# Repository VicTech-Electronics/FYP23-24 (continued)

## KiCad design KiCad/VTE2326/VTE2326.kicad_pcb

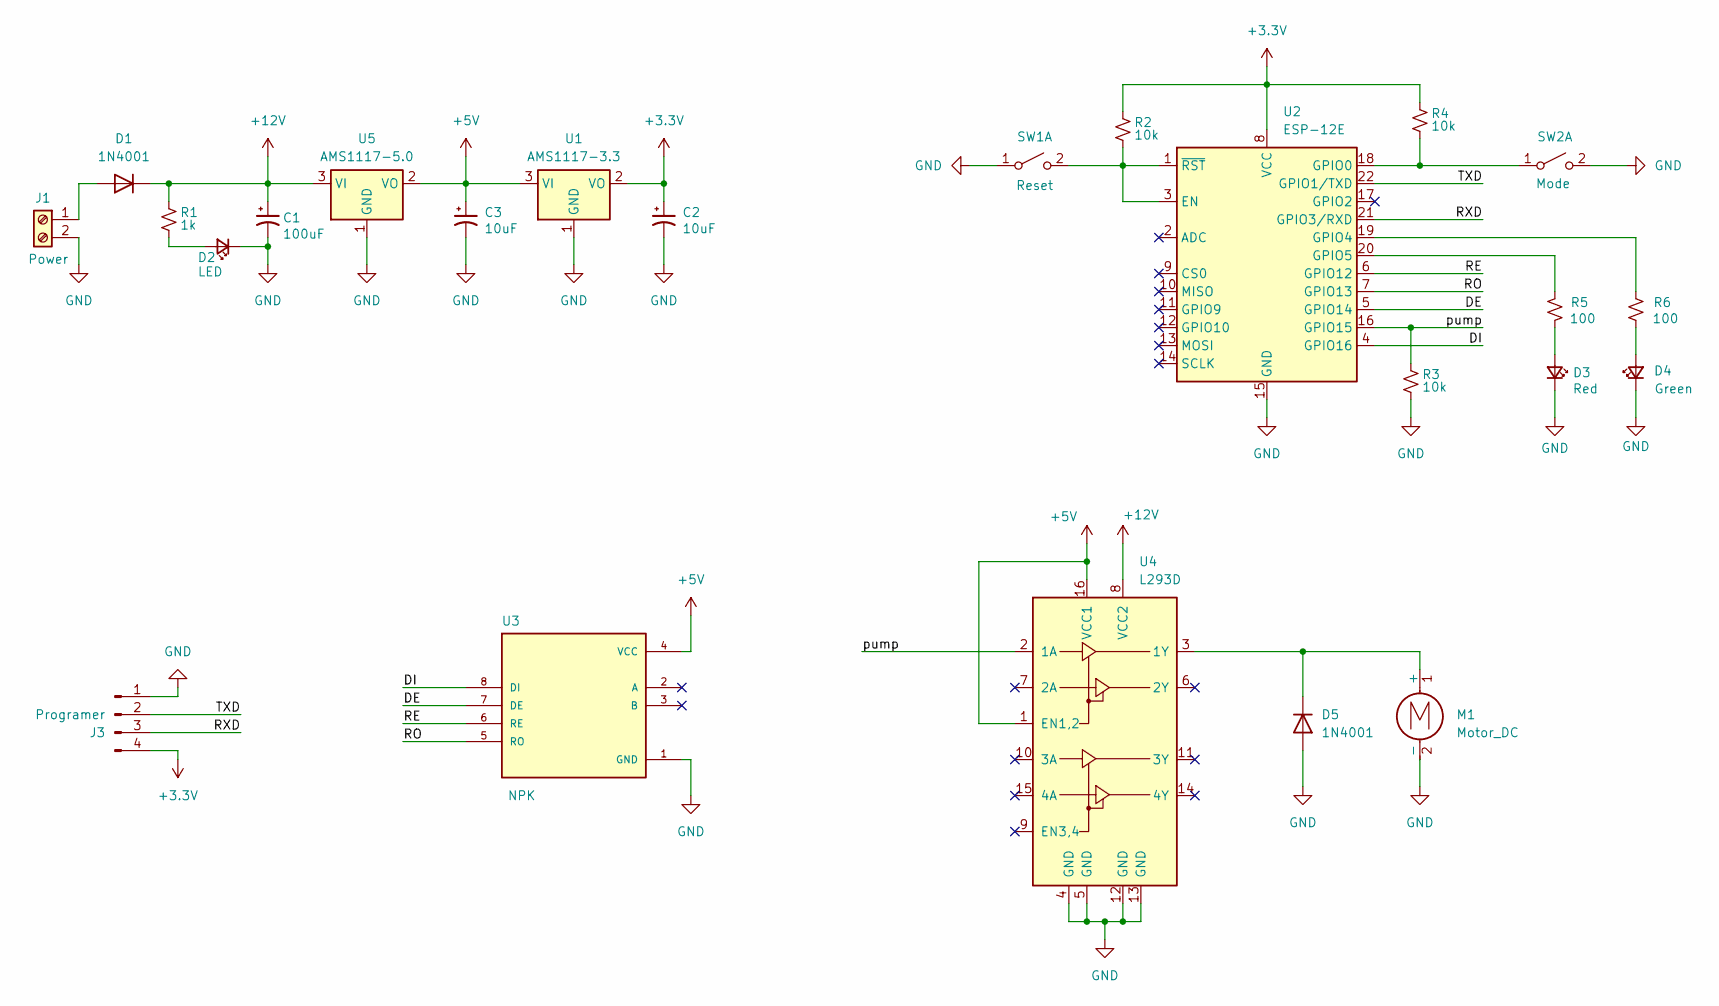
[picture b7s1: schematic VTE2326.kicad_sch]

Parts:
C1: 100uF; CP_Radial_D4.0mm_P2.00mm
C2, C3: 10uF; CP_Radial_D4.0mm_P2.00mm
D1, D5: 1N4001; D_DO-41_SOD81_P10.16mm_Horizontal
D2: LED; LED_D3.0mm_Clear
D3: Red; LED_D3.0mm_Clear
D4: Green; LED_D3.0mm_Clear
J1: Power; TerminalBlock_bornier-2_P5.08mm
J3: Programer; PinHeader_1x04_P2.54mm_Vertical
M1: Motor_DC; TerminalBlock_bornier-2_P5.08mm
R1: 1k; R_Axial_DIN0207_L6.3mm_D2.5mm_P10.16mm_Horizontal
R2, R3, R4: 10k; R_Axial_DIN0207_L6.3mm_D2.5mm_P10.16mm_Horizontal
R5, R6: 100; R_Axial_DIN0207_L6.3mm_D2.5mm_P10.16mm_Horizontal
SW1: Reset; SW_PUSH_6mm
SW2: Mode; SW_PUSH_6mm
U1: AMS1117-3.3; SOT-223-3_TabPin2
U2: ESP-12E
U3: NPK; MODULE_MAX485_MODULE_5V_LOGIC_TLL_TO_RS-485_CONVERTER; PARTREV 1r0
U4: L293D; DIP-16_W7.62mm
U5: AMS1117-5.0; SOT-223-3_TabPin2

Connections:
+3.3V: C2.1, J3.4, R2.1, R4.1, U1.2 (VO), U2.8 (VCC)
+5V: C3.1, U1.3 (VI), U3.4 (VCC), U4.1 (EN1,2), U4.16 (VCC1), U5.2 (VO)
+12V: C1.1, D1.1 (K), R1.1, U4.8 (VCC2), U5.3 (VI)
/DE: U2.5 (GPIO14), U3.7 (DE)
/DI: U2.4 (GPIO16), U3.8 (DI)
/RE: U2.6 (GPIO12), U3.6 (RE)
/RO: U2.7 (GPIO13), U3.5 (RO)
/RXD: J3.3, U2.21 (GPIO3/RXD)
/TXD: J3.2, U2.22 (GPIO1/TXD)
/pump: R3.1, U2.16 (GPIO15), U4.2 (1A)
GND: C1.2, C2.2, C3.2, D2.1 (K), D3.1 (K), D4.1 (K), D5.2 (A), J1.2, J3.1, M1.2 (-), R3.2, SW1.1 (A), SW2.2 (B), U1.1 (GND), U2.15 (GND), U3.1 (GND), U4.4 (GND), U4.5 (GND), U4.12 (GND), U4.13 (GND), U5.1 (GND)
unnamed: D1.2 (A), J1.1
unnamed: D2.2 (A), R1.2
unnamed: D3.2 (A), R5.2
unnamed: D4.2 (A), R6.1
unnamed: D5.1 (K), M1.1 (+), U4.3 (1Y)
unnamed: R2.2, SW1.2 (B), U2.1 (~RST), U2.3 (EN)
unnamed: R4.2, SW2.1 (A), U2.18 (GPIO0)
unnamed: R6.2, U2.19 (GPIO4)
unnamed: R5.1, U2.20 (GPIO5)

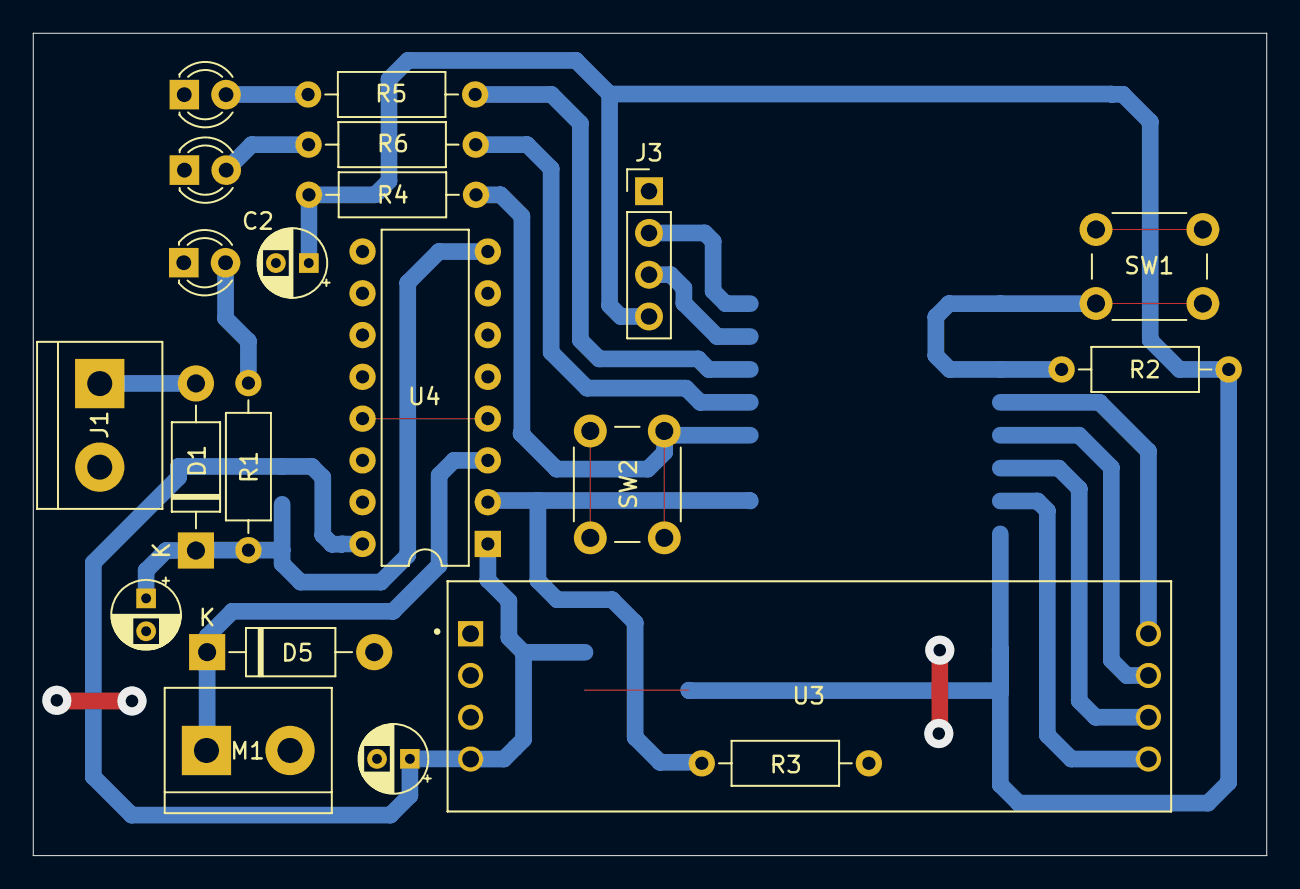
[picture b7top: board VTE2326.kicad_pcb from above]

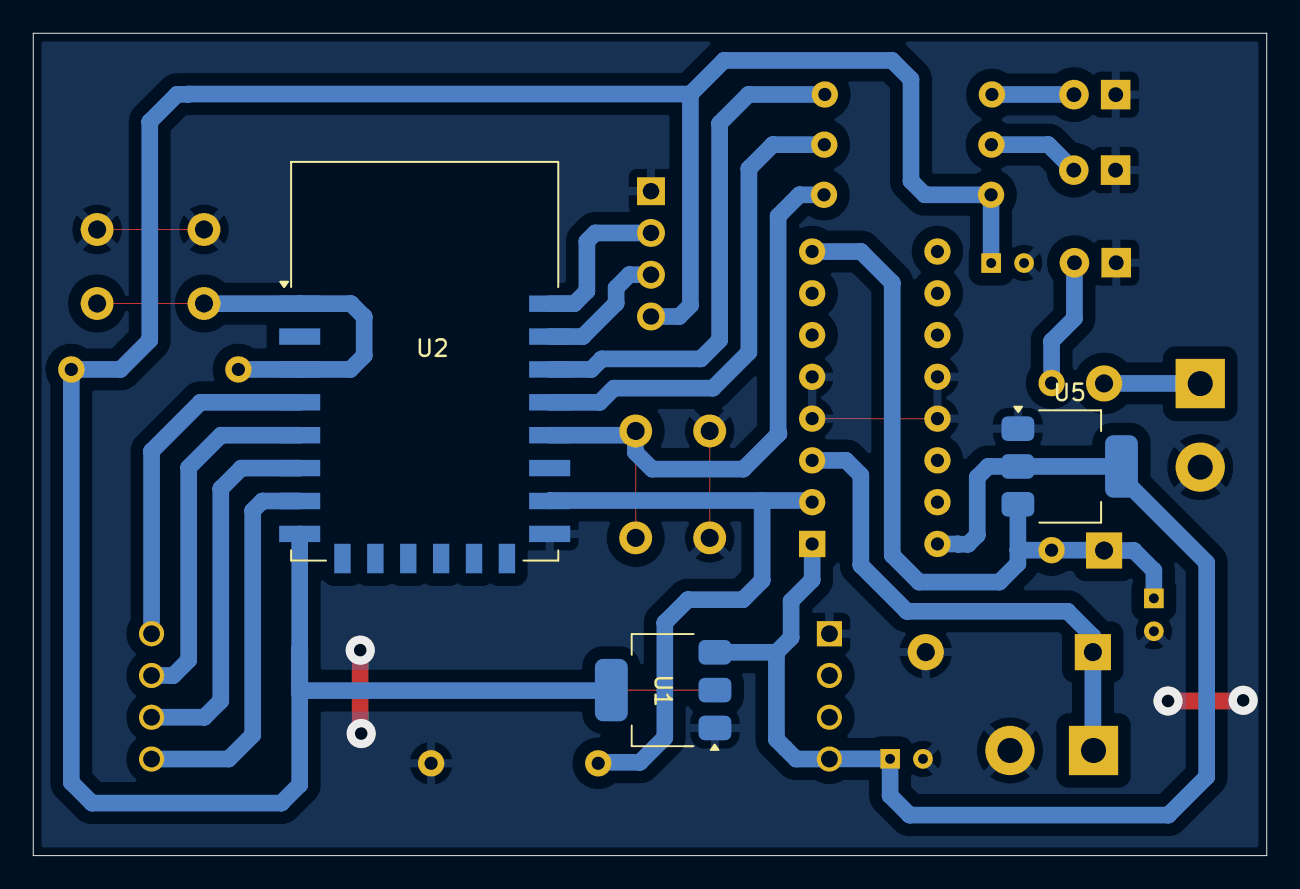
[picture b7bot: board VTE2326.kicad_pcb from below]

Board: 2 copper layers, 75.0 x 50.0 mm, 24 parts (3 on the bottom side), 20 nets.

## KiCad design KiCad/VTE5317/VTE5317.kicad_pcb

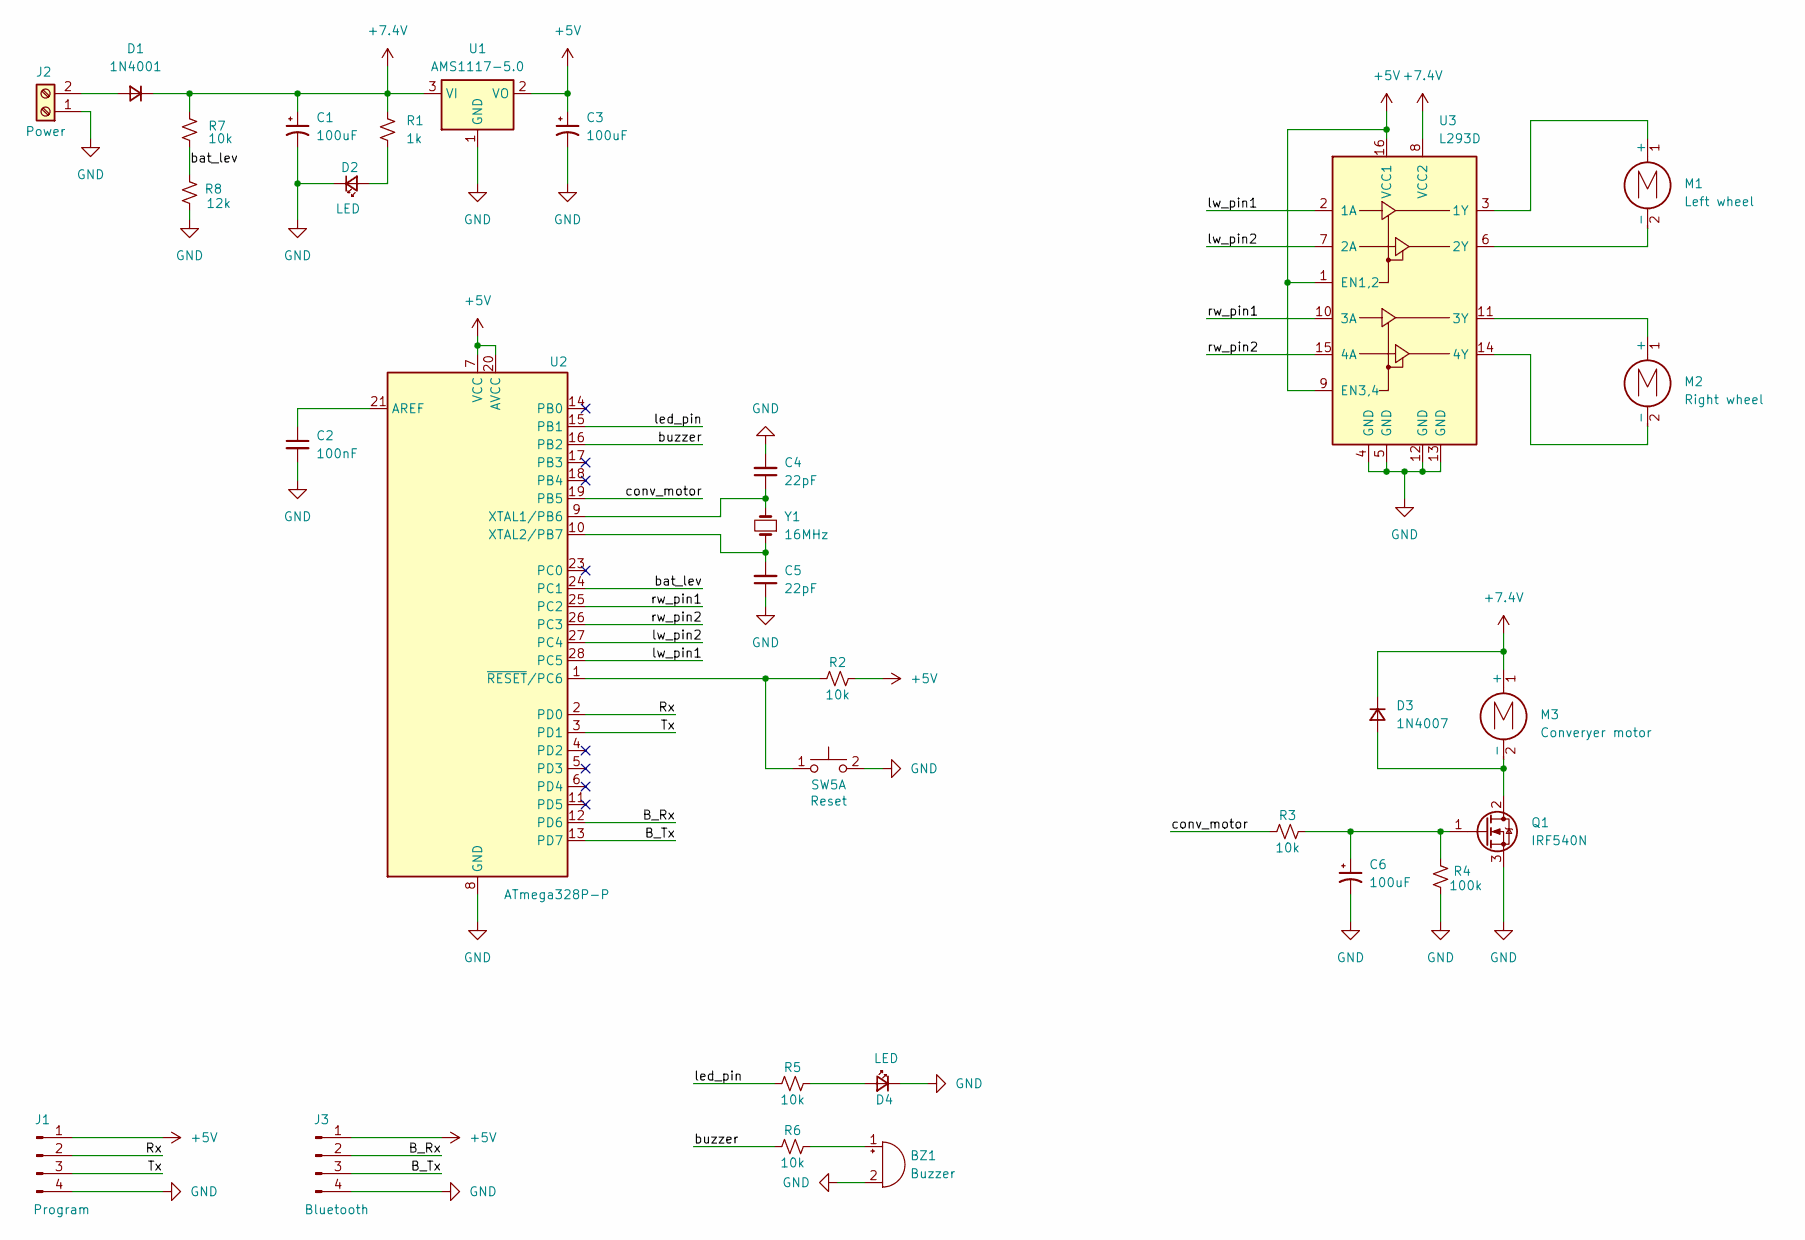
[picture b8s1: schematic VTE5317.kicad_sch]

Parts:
BZ1: Buzzer; Buzzer_12x9.5RM7.6
C1, C3, C6: 100uF; CP_Radial_D5.0mm_P2.50mm
C2: 100nF; C_Disc_D3.0mm_W1.6mm_P2.50mm
C4, C5: 22pF; C_Disc_D3.0mm_W1.6mm_P2.50mm
D1: 1N4001; D_A-405_P10.16mm_Horizontal
D2, D4: LED; LED_D3.0mm
D3: 1N4007; D_A-405_P10.16mm_Horizontal
J1: Program; PinHeader_1x04_P2.54mm_Vertical
J2: Power; TerminalBlock_bornier-2_P5.08mm
J3: Bluetooth; PinHeader_1x04_P2.54mm_Vertical
M1: Left wheel; TerminalBlock_bornier-2_P5.08mm
M2: Right wheel; TerminalBlock_bornier-2_P5.08mm
M3: Converyer motor; TerminalBlock_bornier-2_P5.08mm
Q1: IRF540N; TO-220-3_Vertical
R1: 1k; R_Axial_DIN0207_L6.3mm_D2.5mm_P10.16mm_Horizontal
R2, R3, R5, R6, R7: 10k; R_Axial_DIN0207_L6.3mm_D2.5mm_P10.16mm_Horizontal
R4: 100k; R_Axial_DIN0207_L6.3mm_D2.5mm_P10.16mm_Horizontal
R8: 12k; R_Axial_DIN0207_L6.3mm_D2.5mm_P10.16mm_Horizontal
SW5: Reset; SW_PUSH_6mm
U1: AMS1117-5.0; SOT-223-3_TabPin2
U2: ATmega328P-P; DIP-28_W7.62mm_LongPads
U3: L293D; DIP-16_W7.62mm_Socket_LongPads
Y1: 16MHz; Crystal_HC50_Vertical

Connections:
+5V: C3.1, J1.1, J3.1, R2.2, U1.2 (VO), U2.7 (VCC), U2.20 (AVCC), U3.1 (EN1,2), U3.9 (EN3,4), U3.16 (VCC1)
+7.4V: C1.1, D1.1 (K), D3.1 (K), M3.1 (+), R1.1, R7.1, U1.3 (VI), U3.8 (VCC2)
/B_Rx: J3.2, U2.12 (PD6)
/B_Tx: J3.3, U2.13 (PD7)
/Rx: J1.2, U2.2 (PD0)
/Tx: J1.3, U2.3 (PD1)
/bat_lev: R7.2, R8.1, U2.24 (PC1)
/buzzer: R6.1, U2.16 (PB2)
/conv_motor: R3.1, U2.19 (PB5)
/led_pin: R5.1, U2.15 (PB1)
/lw_pin1: U2.28 (PC5), U3.2 (1A)
/lw_pin2: U2.27 (PC4), U3.7 (2A)
/rw_pin1: U2.25 (PC2), U3.10 (3A)
/rw_pin2: U2.26 (PC3), U3.15 (4A)
GND: BZ1.2 (-), C1.2, C2.2, C3.2, C4.2, C5.1, C6.2, D2.1 (K), D4.1 (K), J1.4, J2.1, J3.4, Q1.3 (S), R4.1, R8.2, SW5.2 (D), U1.1 (GND), U2.8 (GND), U2.22 (GND), U3.4 (GND), U3.5 (GND), U3.12 (GND), U3.13 (GND)
unnamed: BZ1.1 (+), R6.2
unnamed: D1.2 (A), J2.2
unnamed: D2.2 (A), R1.2
unnamed: D3.2 (A), M3.2 (-), Q1.2 (D)
unnamed: D4.2 (A), R5.2
unnamed: M1.1 (+), U3.3 (1Y)
unnamed: M1.2 (-), U3.6 (2Y)
unnamed: M2.1 (+), U3.11 (3Y)
unnamed: M2.2 (-), U3.14 (4Y)
unnamed: C6.1, Q1.1 (G), R3.2, R4.2
unnamed: R2.1, SW5.1 (C), U2.1 (~RESET/PC6)
unnamed: C2.1, U2.21 (AREF)
unnamed: C4.1, U2.9 (XTAL1/PB6), Y1.2
unnamed: C5.2, U2.10 (XTAL2/PB7), Y1.1

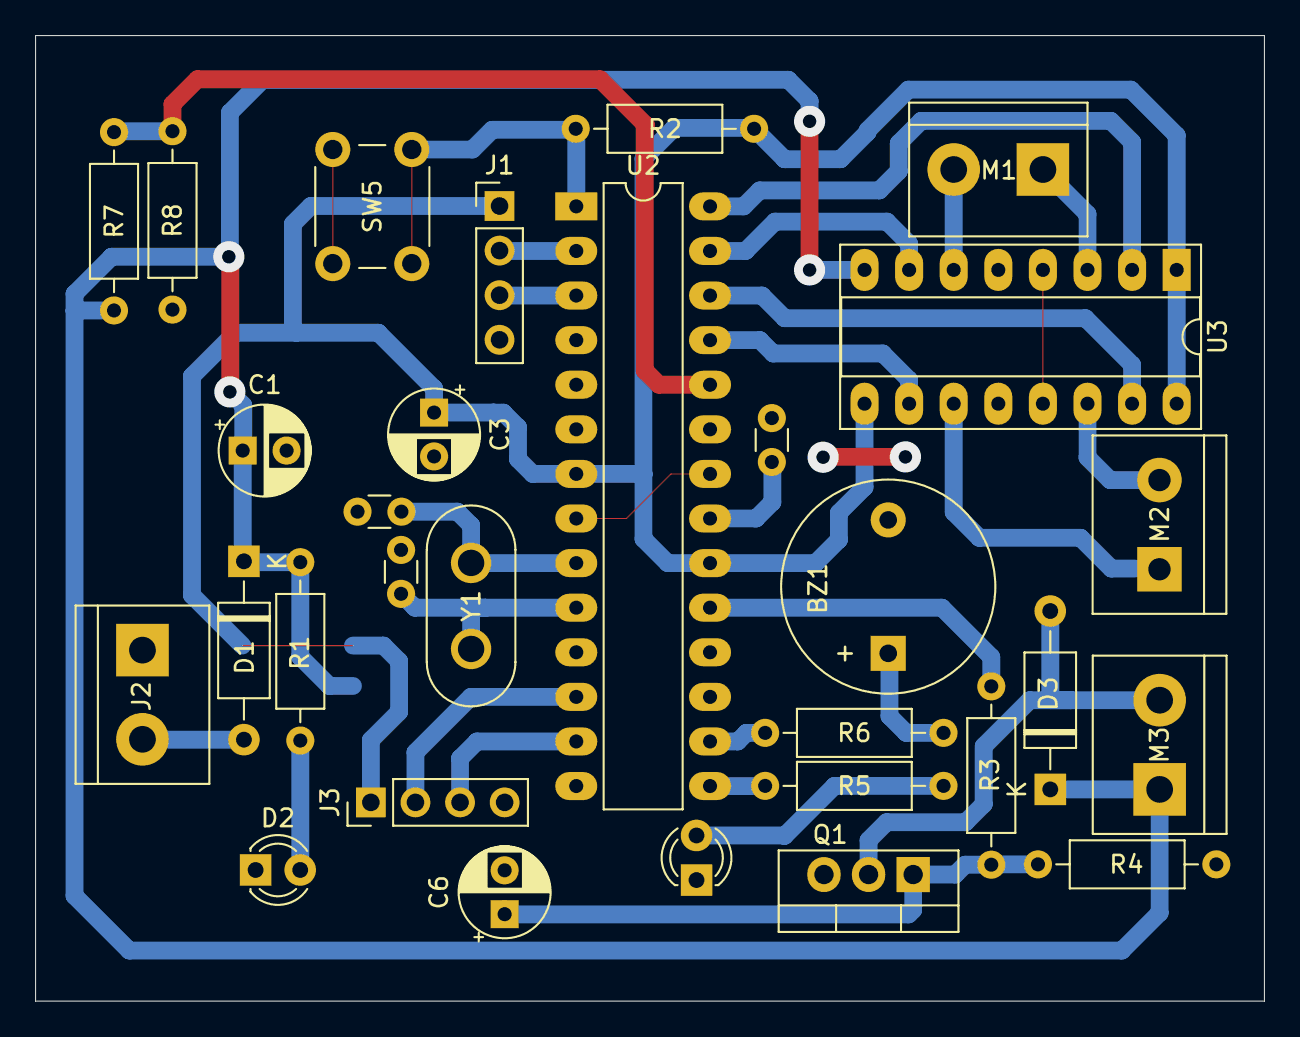
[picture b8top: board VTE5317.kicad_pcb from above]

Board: 2 copper layers, 70.0 x 55.0 mm, 31 parts (1 on the bottom side), 29 nets.

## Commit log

2024-04-30 New commit to push for the first time
2024-05-01 Adding the PCB layout to VTE8788
2024-05-20 latest updated
2024-05-25 Add codes for Mimi's hardware project
